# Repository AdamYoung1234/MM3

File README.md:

Adaptor board for PIC12C508A SOIC8 package.

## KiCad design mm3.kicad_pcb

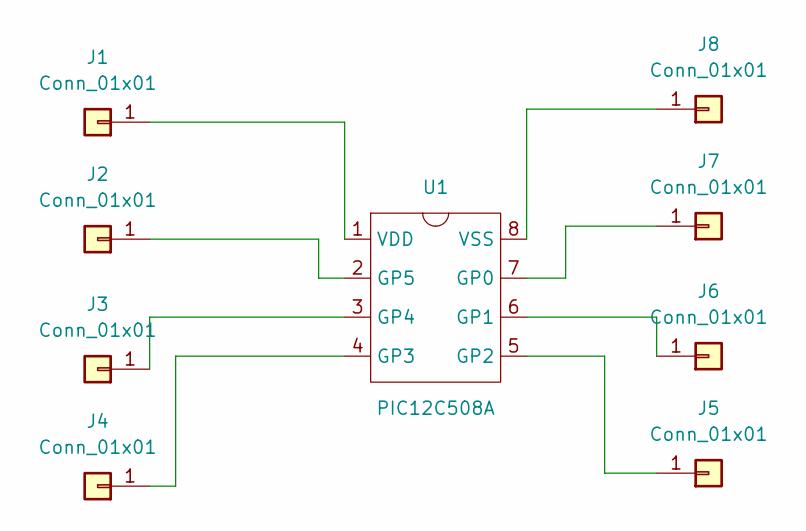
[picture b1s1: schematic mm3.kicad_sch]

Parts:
J1, J2, J3, J4, J5, J6, J7, J8: Conn_01x01; TestPoint_Pad_D1.5mm
U1: PIC12C508A; SOIC-8_3.9x4.9mm_P1.27mm

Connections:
unnamed: J1.1, U1.1 (VDD)
unnamed: J2.1, U1.2 (GP5)
unnamed: J3.1, U1.3 (GP4)
unnamed: J4.1, U1.4 (GP3)
unnamed: J5.1, U1.5 (GP2)
unnamed: J6.1, U1.6 (GP1)
unnamed: J7.1, U1.7 (GP0)
unnamed: J8.1, U1.8 (VSS)

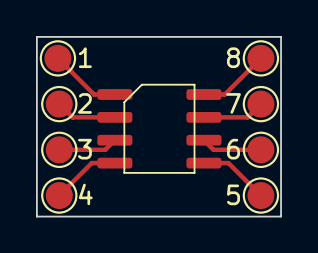
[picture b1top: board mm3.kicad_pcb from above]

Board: 2 copper layers, 13.6 x 10.0 mm, 9 parts (0 on the bottom side), 8 nets.
